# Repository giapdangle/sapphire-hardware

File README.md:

sapphire-hardware
=================

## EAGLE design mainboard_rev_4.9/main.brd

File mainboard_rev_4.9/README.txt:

Blue Sapphire
Schematic notes

CP2104 USB power:
The CP2104 is powered by VUSB, 5 volts direct from the USB connector (J2). VUSB flows through D1 to energize V_IN and the main regulator, unless a supply of higher voltage is applied to the DC input (J1). VUSB is fused at 500 mA in case a short circuit is connected to the DC input. The CP2104 itself is powered from VUSB and it's internal 3.4 volt regulator. 

The IO supply is directly connected to the CP2104 internal 3.4 volt supply. This is within the tolerance range of the 3.3 volt IO on the AVR microcontroller, however, it does mean that this board cannot be used with a main regulator (U2) at less than 3.3 volts. The advantage to this configuration is that the CP2104 is only (and entirely) powered by VUSB.  If there is no USB connection, the CP2104 will draw no current whatsoever. If the CP2104 VIO pin is connected to the main 3.3 volt board supply, it will leak several hundred microamps, even with the rest of the CP2104 unpowered.

CP2104 notes:
The EEPROM config for Vendor ID, S/N, etc can only be programmed once. This is a stark contrast to the FTDI parts. Note that C14 is required for EEPROM programming.

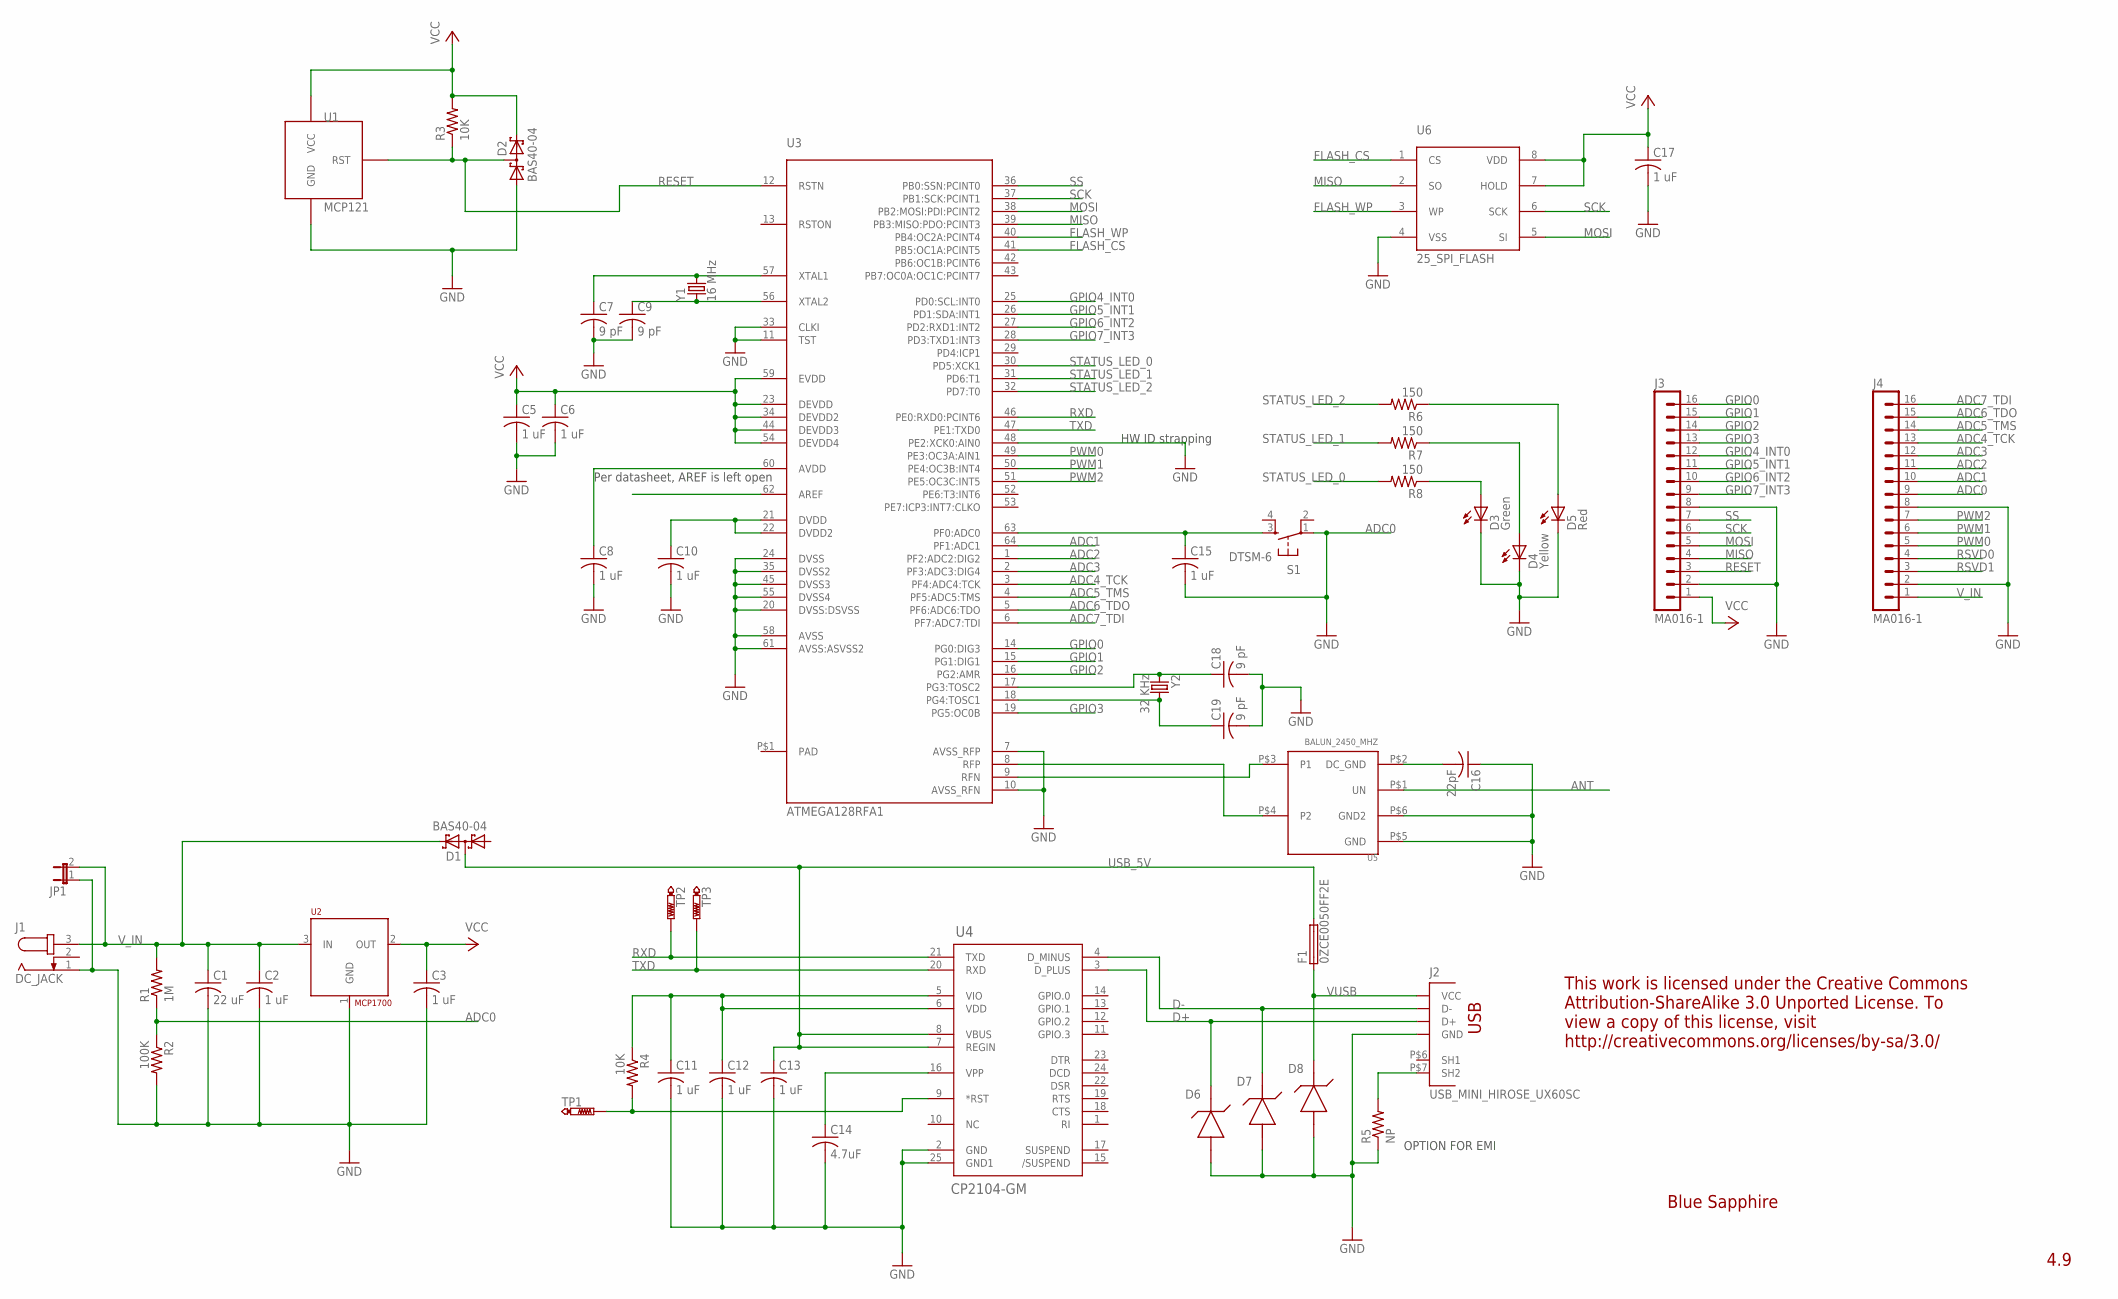
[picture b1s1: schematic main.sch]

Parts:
C1: 22 uF; C0805K
C2, C3, C5, C6, C8, C10, C11, C12, C13, C15, C17: 1 uF; C0603K
C7, C9, C18, C19: 9 pF; C0603K
C14: 4.7uF; C0805K
C16: 22pF; C0603K
D1, D2: BAS40-04; SOT23
D3: Green; CHIPLED_0805
D4: Yellow; CHIPLED_0805
D5: Red; CHIPLED_0805
D6, D7, D8: CG0603MLC; C0603
F1: 0ZCE0050FF2E; C0805
J1: DC_JACK; CONN_DC_JACK
J2: USB_MINI_HIROSE_UX60SC; USB-MINI-B_HIROSE_UX60SC
J3, J4: MA016-1
JP1: JP1E; JP1
R1: 1M; R0603
R2: 100K; R0603
R3, R4: 10K; R0603
R5: NP; R0603
R6, R7, R8: 150; R0603
S1: DTSM-6
TP1, TP2, TP3: PTR1B1,27; B1,27
U1: MCP121; SOT23
U2: MCP1700; SOT23
U3: ATMEGA128RFA1; MLF64
U4: CP2104-GM; QFN24_4X4
U5: BALUN_2450_MHZ; BALUN_0805
U6: 25_SPI_FLASH; SO-8WIDE
Y1: 16 MHz; XTAL_3.2X2.5
Y2: 32 KHz; XTAL_3.2X1.5

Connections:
ADC0: C15.1, J4.9, R1.1, R2.1, S1.3, U3.63 (PF0:ADC0)
ADC1: J4.10, U3.64 (PF1:ADC1)
ADC2: J4.11, U3.1 (PF2:ADC2:DIG2)
ADC3: J4.12, U3.2 (PF3:ADC3:DIG4)
ADC4_TCK: J4.13, U3.3 (PF4:ADC4:TCK)
ADC5_TMS: J4.14, U3.4 (PF5:ADC5:TMS)
ADC6_TDO: J4.15, U3.5 (PF6:ADC6:TDO)
ADC7_TDI: J4.16, U3.6 (PF7:ADC7:TDI)
ANT: U5.P$1 (UN)
AREF: U3.62 (AREF)
AVDD: C8.1, U3.60 (AVDD)
D+: D6.2 (LINE), J2.P$3 (D+), U4.3 (D_PLUS)
D-: D7.2 (LINE), J2.P$2 (D-), U4.4 (D_MINUS)
DVDD: C10.1, U3.21 (DVDD), U3.22 (DVDD2)
FLASH_CS: U3.41 (PB5:OC1A:PCINT5), U6.1 (CS)
FLASH_WP: U3.40 (PB4:OC2A:PCINT4), U6.3 (WP)
GND: C1.2, C2.2, C3.2, C5.2, C6.2, C7.2, C8.2, C9.2, C10.2, C11.2, C12.2, C13.2, C14.2, C15.2, C16.1, C17.2, C18.2, C19.2, D2.1 (A1), D3.C, D4.C, D5.C, D6.1 (GND), D7.1 (GND), D8.1 (GND), J1.1, J2.P$5 (GND), J3.2, J3.8, J4.2, J4.8, JP1.1, R2.2, R5.1, S1.1, U1.3 (GND), U2.1 (GND), U3.7 (AVSS_RFP), U3.10 (AVSS_RFN), U3.11 (TST), U3.20 (DVSS:DSVSS), U3.24 (DVSS), U3.33 (CLKI), U3.35 (DVSS2), U3.45 (DVSS3), U3.48 (PE2:XCK0:AIN0), U3.55 (DVSS4), U3.58 (AVSS), U3.61 (AVSS:ASVSS2), U4.2 (GND), U4.25 (GND1), U5.P$5 (GND), U5.P$6 (GND2), U6.4 (VSS)
GPIO0: J3.16, U3.14 (PG0:DIG3)
GPIO1: J3.15, U3.15 (PG1:DIG1)
GPIO2: J3.14, U3.16 (PG2:AMR)
GPIO3: J3.13, U3.19 (PG5:OC0B)
GPIO4_INT0: J3.12, U3.25 (PD0:SCL:INT0)
GPIO5_INT1: J3.11, U3.26 (PD1:SDA:INT1)
GPIO6_INT2: J3.10, U3.27 (PD2:RXD1:INT2)
GPIO7_INT3: J3.9, U3.28 (PD3:TXD1:INT3)
MISO: J3.4, U3.39 (PB3:MISO:PDO:PCINT3), U6.2 (SO)
MOSI: J3.5, U3.38 (PB2:MOSI:PDI:PCINT2), U6.5 (SI)
unnamed: C16.2, U5.P$2 (DC_GND)
unnamed: C19.1, U3.18 (PG4:TOSC1), Y2.P$2 (2)
unnamed: U3.8 (RFP), U5.P$4 (P2)
unnamed: R4.2, TP1.TP, U4.9 (*RST)
unnamed: D3.A, R8.1
unnamed: J2.P$7 (SH2), R5.2
unnamed: D4.A, R7.1
unnamed: D5.A, R6.1
unnamed: U3.9 (RFN), U5.P$3 (P1)
unnamed: C18.1, U3.17 (PG3:TOSC2), Y2.P$1 (1)
unnamed: C14.1, U4.16 (VPP)
PWM0: J4.5, U3.49 (PE3:OC3A:AIN1)
PWM1: J4.6, U3.50 (PE4:OC3B:INT4)
PWM2: J4.7, U3.51 (PE5:OC3C:INT5)
RESET: D2.3 (C1A2), J3.3, R3.1, U1.1 (RST), U3.12 (RSTN)
RSVD0: J4.4
RSVD1: J4.3
RXD: TP2.TP, U3.46 (PE0:RXD0:PCINT6), U4.21 (TXD)
SCK: J3.6, U3.37 (PB1:SCK:PCINT1), U6.6 (SCK)
SS: J3.7, U3.36 (PB0:SSN:PCINT0)
STATUS_LED_0: R8.2, U3.30 (PD5:XCK1)
STATUS_LED_1: R7.2, U3.31 (PD6:T1)
STATUS_LED_2: R6.2, U3.32 (PD7:T0)
TXD: TP3.TP, U3.47 (PE1:TXD0), U4.20 (RXD)
USB_5V: C13.1, D1.3 (C1A2), F1.2, U4.7 (REGIN), U4.8 (VBUS)
USB_VDD: C11.1, C12.1, R4.1, U4.5 (VIO), U4.6 (VDD)
VCC: C3.1, C5.1, C6.1, C17.1, D2.2 (C2), J3.1, R3.2, U1.2 (VCC), U2.2 (OUT), U3.23 (DEVDD), U3.34 (DEVDD2), U3.44 (DEVDD3), U3.54 (DEVDD4), U3.59 (EVDD), U6.7 (HOLD), U6.8 (VDD)
VUSB: D8.2 (LINE), F1.1, J2.P$1 (VCC)
V_IN: C1.1, C2.1, D1.2 (C2), J1.3, J4.1, JP1.2, R1.2, U2.3 (IN)
XTAL1: C7.1, U3.57 (XTAL1), Y1.P$3 (2)
XTAL2: C9.1, U3.56 (XTAL2), Y1.P$1 (1)

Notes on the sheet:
Per datasheet, AREF is left open
HW ID strapping
OPTION FOR EMI
Blue Sapphire
4.9
This work is licensed under the Creative Commons Attribution-ShareAlike 3.0 Unported License. To view a copy of this license, visit http://creativecommons.org/licenses/by-sa/3.0/

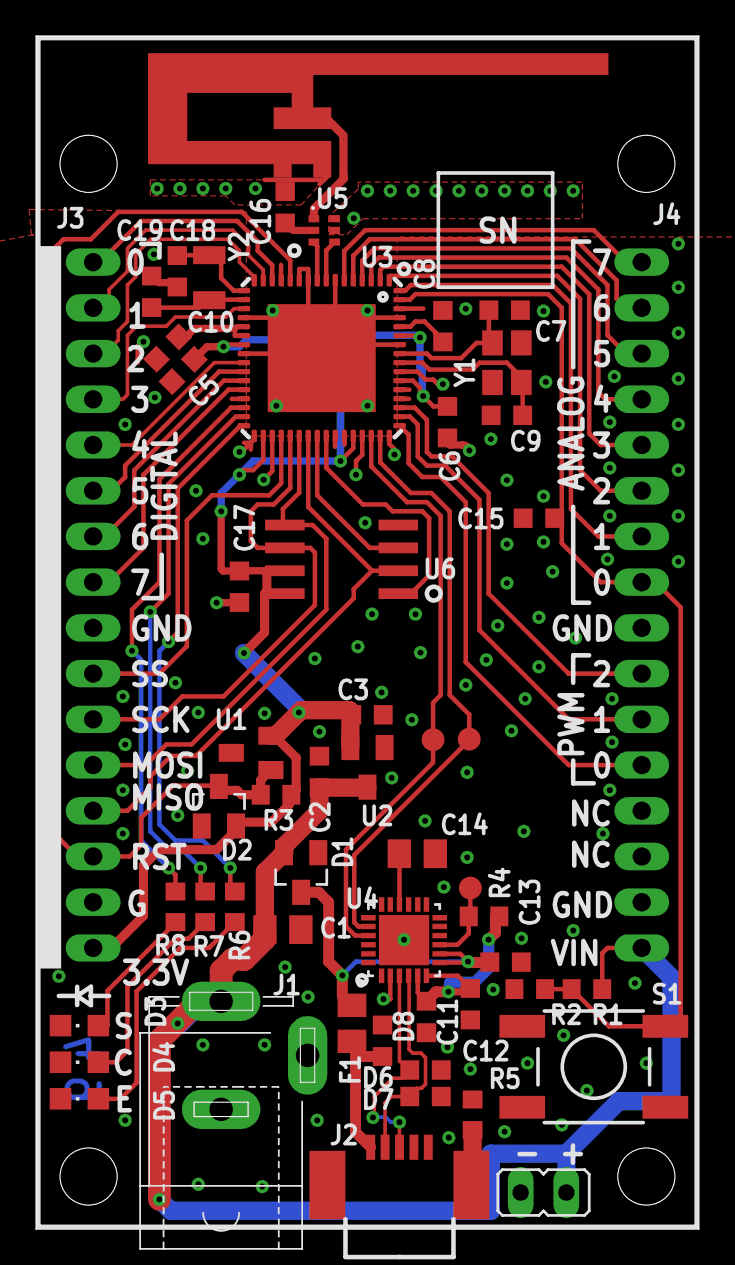
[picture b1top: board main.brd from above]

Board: 2 copper layers, 36.8 x 66.3 mm, 53 parts (0 on the bottom side), 54 nets.

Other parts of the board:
ANT: F_ANTENNA_2_4GHZ

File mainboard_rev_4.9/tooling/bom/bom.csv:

Line item,Digikey PN,Description,Qty per unit,Ref Des,Notes
1,311-10KGRCT-ND,"Res, 10K, 0603",2,"R3, R4",
2,311-100KGRCT-ND,"Res, 100K, 0603",1,R2,
3,311-150GRCT-ND,"Res, 150, 0603",3,"R6, R7, R8",
4,490-3895-1-ND,"Cap, 1u, 0603",11,"C2, C3, C5, C6, C8, C10, C11, C12, C13, C15, C17",
5,445-6797-1-ND,"Cap, 22u, 0805",1,C1,
6,311-1371-1-ND,"Cap, 4.7u 0805",1,C14,
7,445-5046-1-ND,"Cap, 9p, 0603",4,"C7, C9, C18, C19",
8,712-1332-1-ND,"Cap, RF, 22p, 0603",1,C16,
9,CG0603MLC-05ECT-ND,"ESD, 0603",3,"D6, D7, D8",
10,507-1519-1-ND,"Fuse, 0805",1,F1,
11,SER3628CT-ND,"Crystal, 16MHz, SMT",1,Y1,
12,887-1505-1-ND,"Crystal, 32KHz, SMT",1,Y2,
13,BAS40-04-FDICT-ND,"Diode, dual series, SOT23",2,"D1, D2",
14,475-1410-1-ND,"LED, green, 0805",1,D3,
15,754-1135-1-ND,"LED, yellow, 0805",1,D4,
16,475-1415-1-ND,"LED, red, 0805",1,D5,
17,ATMEGA128RFA1-ZU-ND,"IC, ATMega128RFA1, QFN64",1,U3,
18,SST25VF080B-80-4I-S2AE-ND,"IC, SPI Flash, 8 MBit, SOIC8",1,U6,
19,712-1538-1-ND,"IC, Balun, 2450 MHz, DFN6",1,U5,
20,MCP1703T-3302E/CBCT-ND,"IC, LDO Reg, 3.3v, SOT23",1,U2,
21,336-2008-5-ND,"IC, CP2104 USB, QFN24",1,U4,
22,MCP121T-195I/LBCT-ND,"IC, MCP121 Reset supervisor, SOT23",1,U1,
23,CP-102A-ND,"Conn, DC Power, PTH",1,J1,
24,H11671CT-ND,"Conn, Mini USB, SMT",1,J2," H11671TR-ND for 1500+, tape and reel"
25,S7014-ND,"Conn, Female header, 1x16, PTH",2,"J3, J4",
26,450-1757-1-ND,"Switch, tactile, SMT, SPST-NO",1,S1,"450-1757-2-ND for 1200+, tape and reel"
27,311-1.0MGRCT-ND,"Res, 100K, 0603",1,R1,

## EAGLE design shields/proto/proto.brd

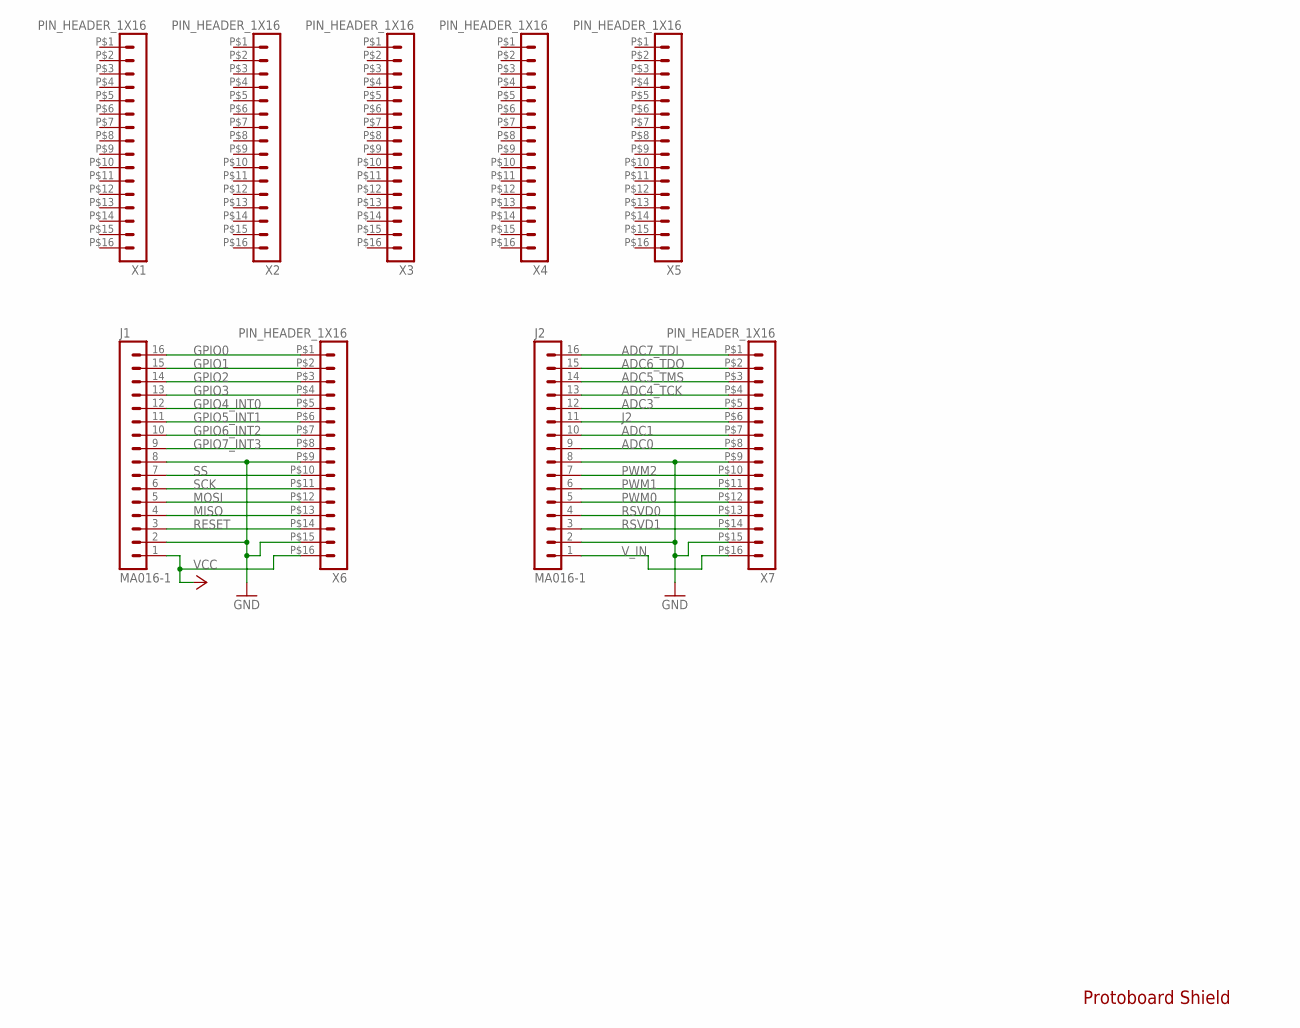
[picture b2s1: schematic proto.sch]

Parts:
J1, J2: MA016-1
X1, X2, X3, X4, X5, X6, X7: PIN_HEADER_1X16

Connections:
ADC0: J2.9, X7.P$8 (8)
ADC1: J2.10, X7.P$7 (7)
ADC3: J2.12, X7.P$5 (5)
ADC4_TCK: J2.13, X7.P$4 (4)
ADC5_TMS: J2.14, X7.P$3 (3)
ADC6_TDO: J2.15, X7.P$2 (2)
ADC7_TDI: J2.16, X7.P$1 (1)
GND: J1.2, J1.8, J2.2, J2.8, X6.P$9 (9), X6.P$15 (15), X7.P$9 (9), X7.P$15 (15)
GPIO0: J1.16, X6.P$1 (1)
GPIO1: J1.15, X6.P$2 (2)
GPIO2: J1.14, X6.P$3 (3)
GPIO3: J1.13, X6.P$4 (4)
GPIO4_INT0: J1.12, X6.P$5 (5)
GPIO5_INT1: J1.11, X6.P$6 (6)
GPIO6_INT2: J1.10, X6.P$7 (7)
GPIO7_INT3: J1.9, X6.P$8 (8)
J2: J2.11, X7.P$6 (6)
MISO: J1.4, X6.P$13 (13)
MOSI: J1.5, X6.P$12 (12)
PWM0: J2.5, X7.P$12 (12)
PWM1: J2.6, X7.P$11 (11)
PWM2: J2.7, X7.P$10 (10)
RESET: J1.3, X6.P$14 (14)
RSVD0: J2.4, X7.P$13 (13)
RSVD1: J2.3, X7.P$14 (14)
SCK: J1.6, X6.P$11 (11)
SS: J1.7, X6.P$10 (10)
VCC: J1.1, X6.P$16 (16)
V_IN: J2.1, X7.P$16 (16)

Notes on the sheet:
Protoboard Shield

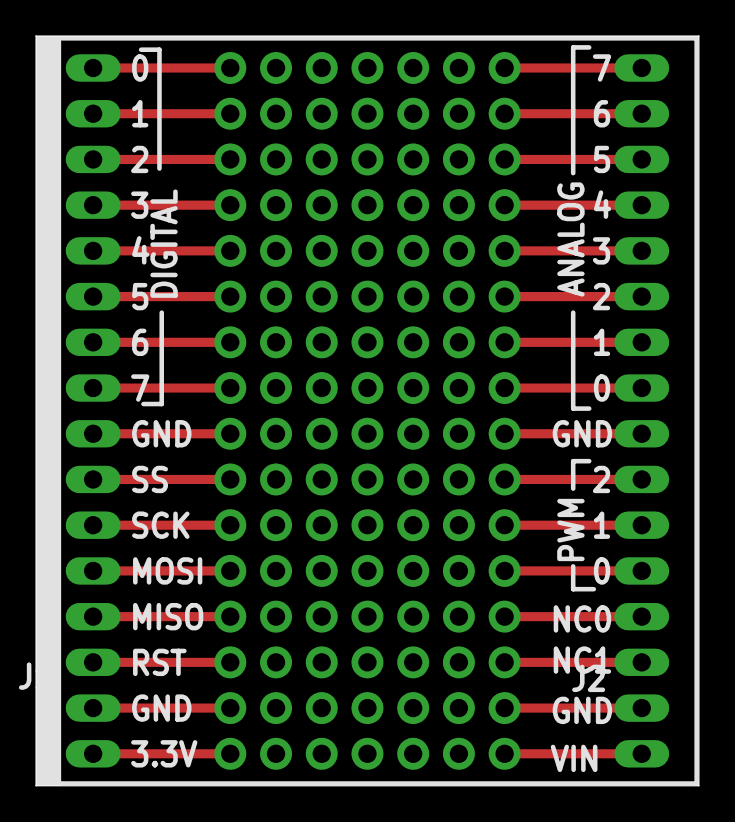
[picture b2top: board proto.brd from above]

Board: 2 copper layers, 36.8 x 41.7 mm, 9 parts (0 on the bottom side), 29 nets.

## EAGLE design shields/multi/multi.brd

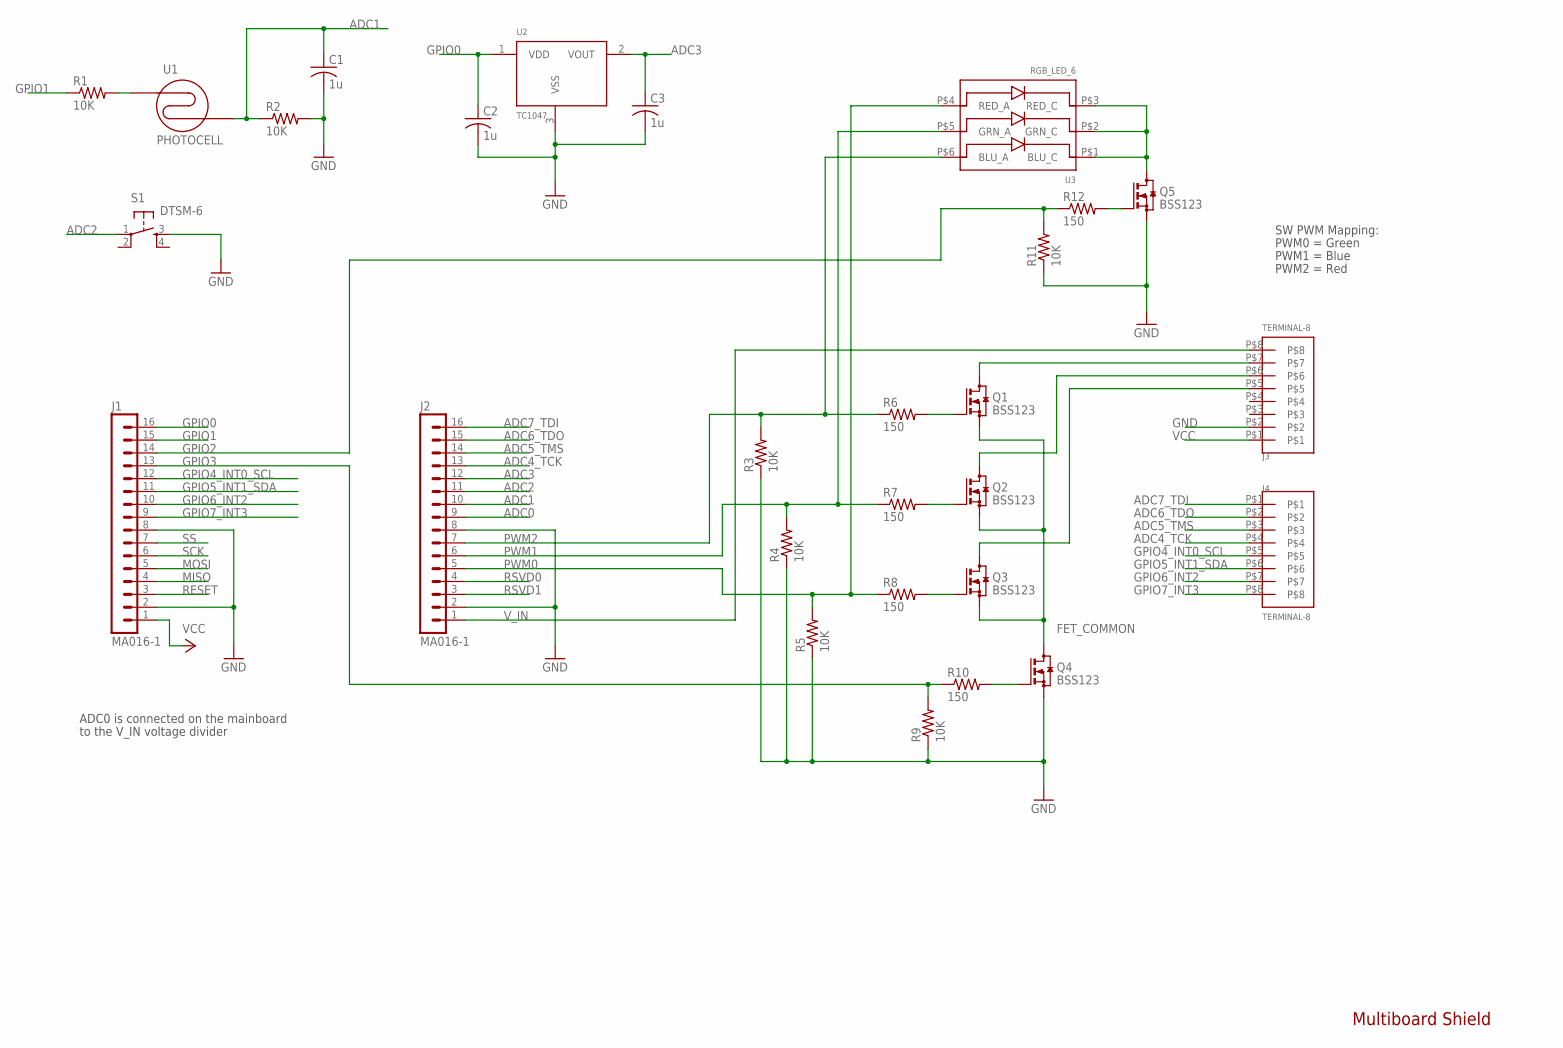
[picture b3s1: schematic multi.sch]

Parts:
C1, C2, C3: 1u; C0603K
J1, J2: MA016-1
J3, J4: TERMINAL-8
Q1, Q2, Q3, Q4, Q5: BSS123; SOT23
R1, R2, R3, R4, R5, R9, R11: 10K; R0603
R6, R7, R8, R10, R12: 150; R0603
S1: DTSM-6
U1: PHOTOCELL
U2: TC1047; SOT23
U3: RGB_LED_6; PLCC6

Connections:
ADC0: J2.9
ADC1: C1.1, J2.10, R2.1, U1.P$2
ADC2: J2.11, S1.1
ADC3: C3.1, J2.12, U2.2 (VOUT)
ADC4_TCK: J2.13, J4.P$4
ADC5_TMS: J2.14, J4.P$3
ADC6_TDO: J2.15, J4.P$2
ADC7_TDI: J2.16, J4.P$1
FET_COMMON: Q1.2 (S), Q2.2 (S), Q3.2 (S), Q4.3 (D)
GND: C1.2, C2.2, C3.2, J1.2, J1.8, J2.2, J2.8, J3.P$2, Q4.2 (S), Q5.2 (S), R2.2, R3.1, R4.1, R5.1, R9.1, R11.1, S1.3, U2.3 (VSS)
GPIO0: C2.1, J1.16, U2.1 (VDD)
GPIO1: J1.15, R1.1
GPIO2: J1.14, R11.2, R12.1
GPIO3: J1.13, R9.2, R10.1
GPIO4_INT0_SCL: J1.12, J4.P$5
GPIO5_INT1_SDA: J1.11, J4.P$6
GPIO6_INT2: J1.10, J4.P$7
GPIO7_INT3: J1.9, J4.P$8
INA: Q2.1 (G), R7.2
INB: Q1.1 (G), R6.2
MISO: J1.4
MOSI: J1.5
unnamed: R1.2, U1.P$1
unnamed: Q5.3 (D), U3.P$1 (BLU_C), U3.P$2 (GRN_C), U3.P$3 (RED_C)
unnamed: Q5.1 (G), R12.2
unnamed: Q3.1 (G), R8.2
unnamed: Q4.1 (G), R10.2
OUT0: J3.P$5, Q3.3 (D)
OUT1: J3.P$6, Q2.3 (D)
OUT2: J3.P$7, Q1.3 (D)
PWM0: J2.5, R5.2, R8.1, U3.P$4 (RED_A)
PWM1: J2.6, R4.2, R7.1, U3.P$5 (GRN_A)
PWM2: J2.7, R3.2, R6.1, U3.P$6 (BLU_A)
RESET: J1.3
RSVD0: J2.4
RSVD1: J2.3
SCK: J1.6
SS: J1.7
VCC: J1.1, J3.P$1
V_IN: J2.1, J3.P$8

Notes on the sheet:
SW PWM Mapping:
PWM0 = Green
PWM1 = Blue
PWM2 = Red
ADC0 is connected on the mainboard
to the V_IN voltage divider
Multiboard Shield

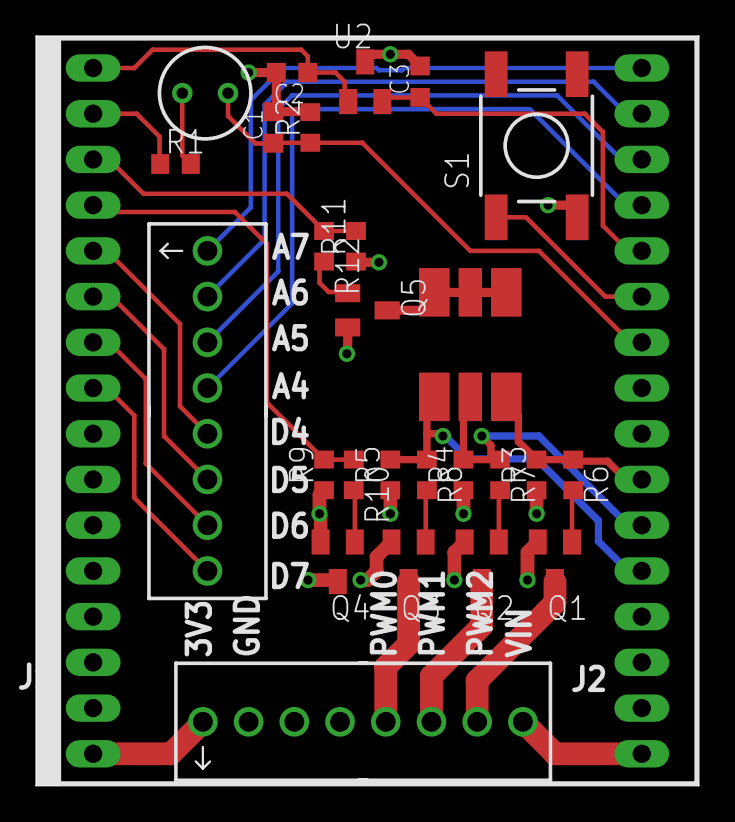
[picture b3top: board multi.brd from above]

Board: 2 copper layers, 36.8 x 41.7 mm, 28 parts (0 on the bottom side), 32 nets.

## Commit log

2013-05-02 Public hardware release
2013-05-02 Generated tooling data
2013-05-06 Added schematic notes and a few missing ref des to PCB
2013-05-06 Added final tooling data
2013-05-06 Removed JP1 from centroid file and added schematic pdf
2013-05-15 Fixed typo in BOM
